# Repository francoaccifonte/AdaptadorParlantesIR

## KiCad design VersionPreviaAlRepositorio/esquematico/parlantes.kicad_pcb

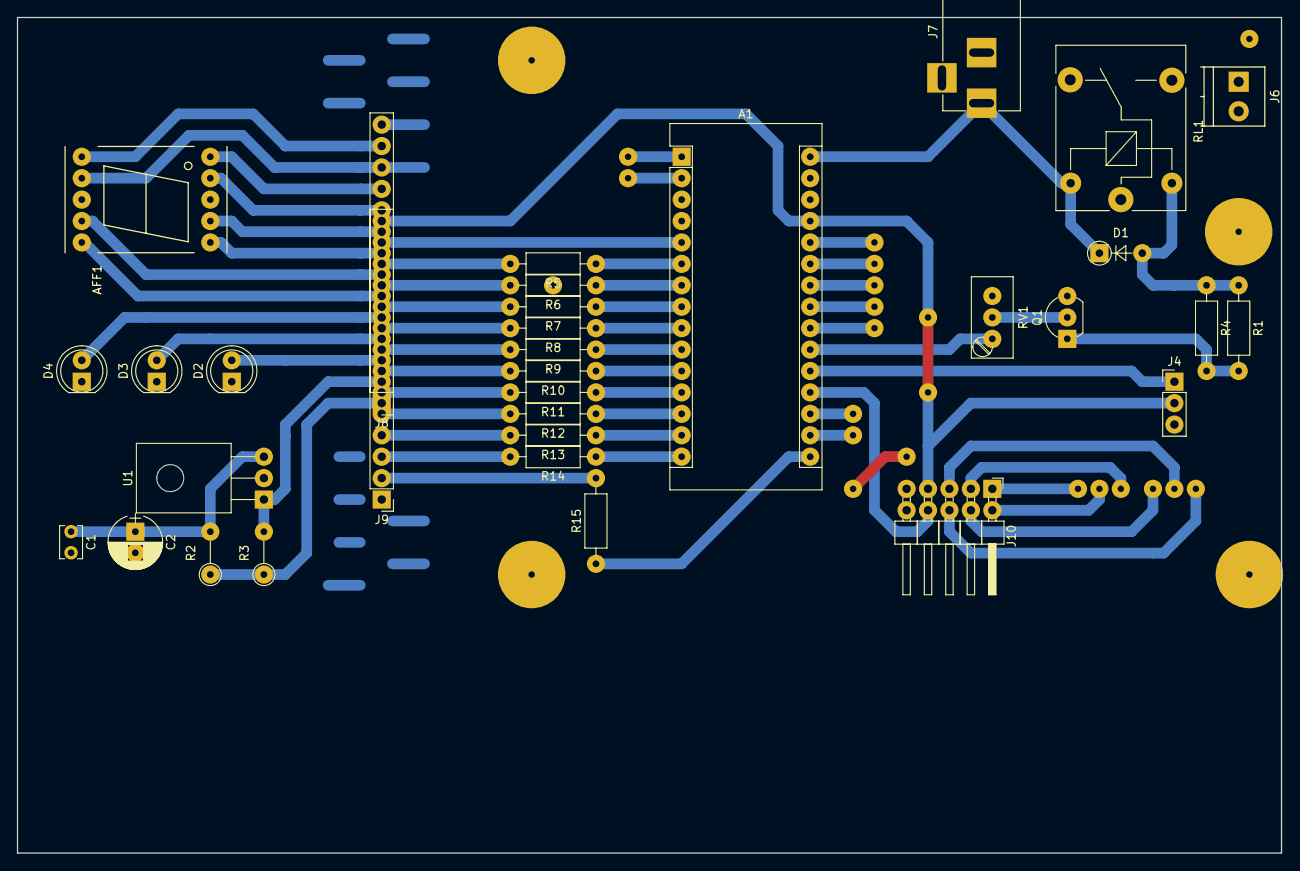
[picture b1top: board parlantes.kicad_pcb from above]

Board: 2 copper layers, 149.9 x 99.1 mm, 37 parts (0 on the bottom side), 49 nets.

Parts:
A1: Arduino_Nano_v3.x; Arduino_Nano
AFF1: LTS-6960HR; 7SegmentLED_LTS6760_LTS6780
C1: C; C_Disc_D3.8mm_W2.6mm_P2.50mm
C2: CP; CP_Radial_D6.3mm_P2.50mm
D1: D; D_A-405_P5.08mm_Vertical_AnodeUp
D2, D3, D4: LED; LED_D5.0mm
J1, J2, J3, J5: Screw_Terminal_1x01; pad_wire
J4: CONN_01X03; Pin_Header_Straight_1x03_Pitch2.54mm
J6: CONN_01X02_FEMALE; TerminalBlock_Pheonix_PT-3.5mm_2pol
J7: dc_jack; BARREL_JACK
J8, J9: CONN_01X14; Pin_Header_Straight_1x14_Pitch2.54mm
J10: CONN_01X10; Pin_Header_Angled_2x05_Pitch2.54mm
Q1: Q_NPN_CBE; TO-92_Inline_Wide
R1, R4: 200; R_Axial_DIN0207_L6.3mm_D2.5mm_P10.16mm_Horizontal
R2: 100; R_Axial_DIN0207_L6.3mm_D2.5mm_P5.08mm_Vertical
R3: 10k; R_Axial_DIN0207_L6.3mm_D2.5mm_P5.08mm_Vertical
R5, R6, R7, R8, R9, R10, R11, R12, R13, R14, R15: R; R_Axial_DIN0207_L6.3mm_D2.5mm_P10.16mm_Horizontal
RL1: FINDER-40.31; Relay_SANYOU_SRD_Series_Form_C
RV1: 100k; Potentiometer_Trimmer_Bourns_3296W
U1: TSDP341xx; TO-126_Horizontal

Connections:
/alt_neg: J6.2, RL1.1
/alt_pos: J6.1, RL1.3
/gnd_slave: AFF1.3, AFF1.8, C1.2, C2.2, D2.1, D3.1, D4.1, U1.2
/ir_rv_out: A1.5, J9.13
/ir_rv_out_slave: J8.2, R3.2, U1.1
/relay_cont: A1.21, RV1.1
/servo_signal: A1.20, J4.1
/vcc_5v: A1.27, J4.2, J9.14, J10.7
/vcc_5v_slave: J8.1, R2.1, R3.1
/vcc_12v: A1.30, D1.1, J7.1, RL1.5
/volumen_fisico: A1.19, J10.8
GND: A1.4, A1.29, J4.3, J7.2, J9.1, J10.9, J10.10, Q1.3, RV1.3
unnamed: A1.6, R5.1
unnamed: A1.7, R6.1
unnamed: A1.8, R7.1
unnamed: A1.9, R8.1
unnamed: A1.10, R9.1
unnamed: A1.11, R10.1
unnamed: A1.12, R11.1
unnamed: A1.13, R12.1
unnamed: A1.14, R13.1
unnamed: A1.15, R14.1
unnamed: A1.16, R15.1
unnamed: AFF1.1, J8.8
unnamed: AFF1.2, J8.9
unnamed: AFF1.4, J8.10
unnamed: AFF1.5, J8.11
unnamed: AFF1.6, J8.13
unnamed: AFF1.7, J8.12
unnamed: AFF1.9, J8.7
unnamed: AFF1.10, J8.6
unnamed: C1.1, C2.1, R2.2, U1.3
unnamed: D1.2, R1.1, R4.1, RL1.2
unnamed: D2.2, J8.3
unnamed: D3.2, J8.4
unnamed: D4.2, J8.5
unnamed: J9.2, R15.2
unnamed: J9.3, R14.2
unnamed: J9.4, R13.2
unnamed: J9.5, R12.2
unnamed: J9.6, R11.2
unnamed: J9.7, R10.2
unnamed: J9.8, R9.2
unnamed: J9.9, R8.2
unnamed: J9.10, R7.2
unnamed: J9.11, R6.2
unnamed: J9.12, R5.2
unnamed: Q1.1, R1.2, R4.2
unnamed: Q1.2, RV1.2

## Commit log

2021-01-03 'kickoff'
2021-01-03 add libs
2021-01-03 moved directory so arduino is happy
2021-01-04 refactored the shit out of it and added manual mode
